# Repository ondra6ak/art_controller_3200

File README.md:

Art Controller 3200
===================

Simple board with ATmega32u4 and isolated DMX512 interface

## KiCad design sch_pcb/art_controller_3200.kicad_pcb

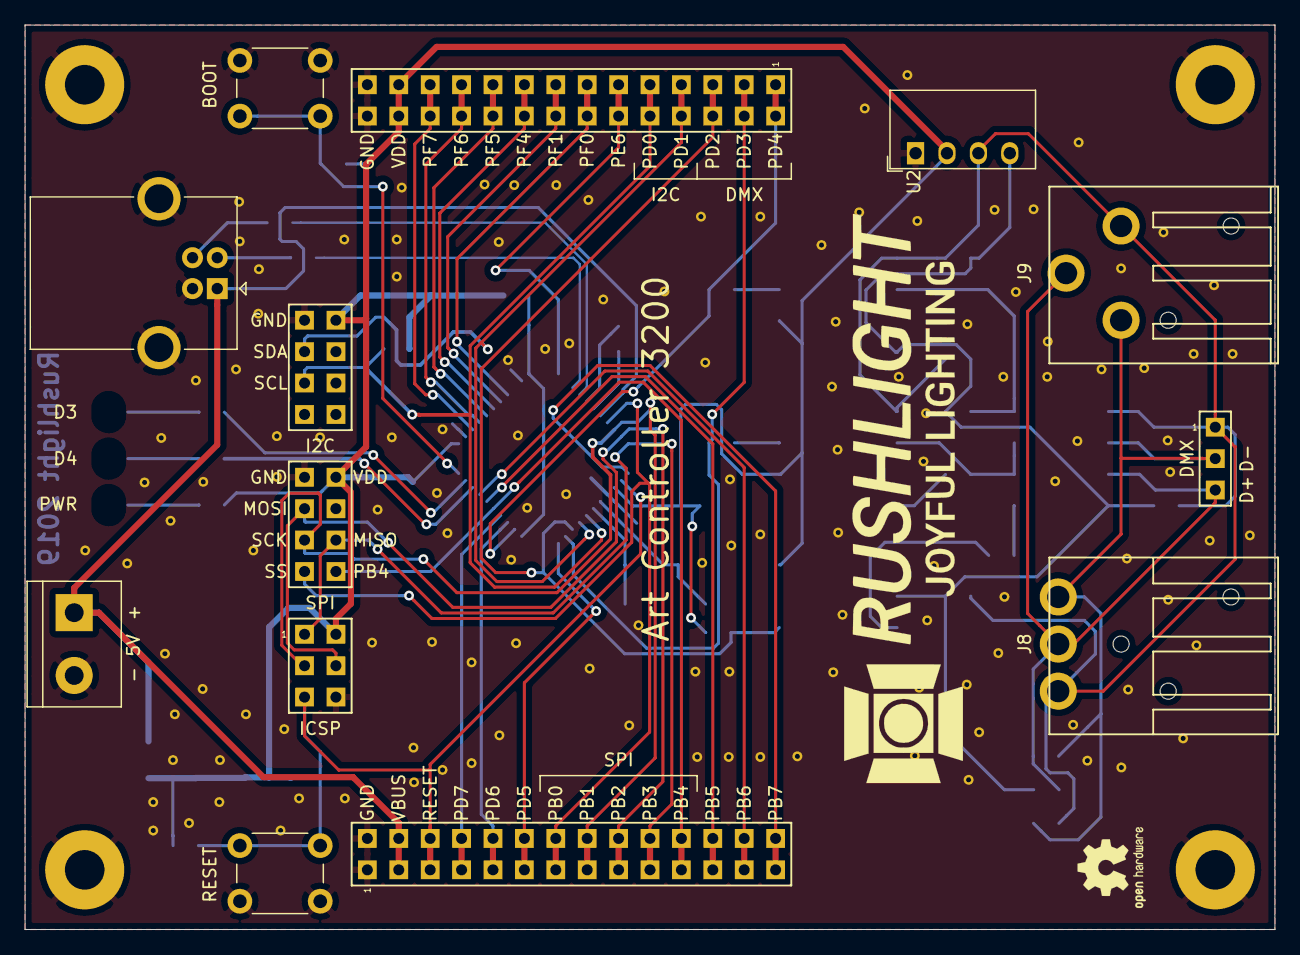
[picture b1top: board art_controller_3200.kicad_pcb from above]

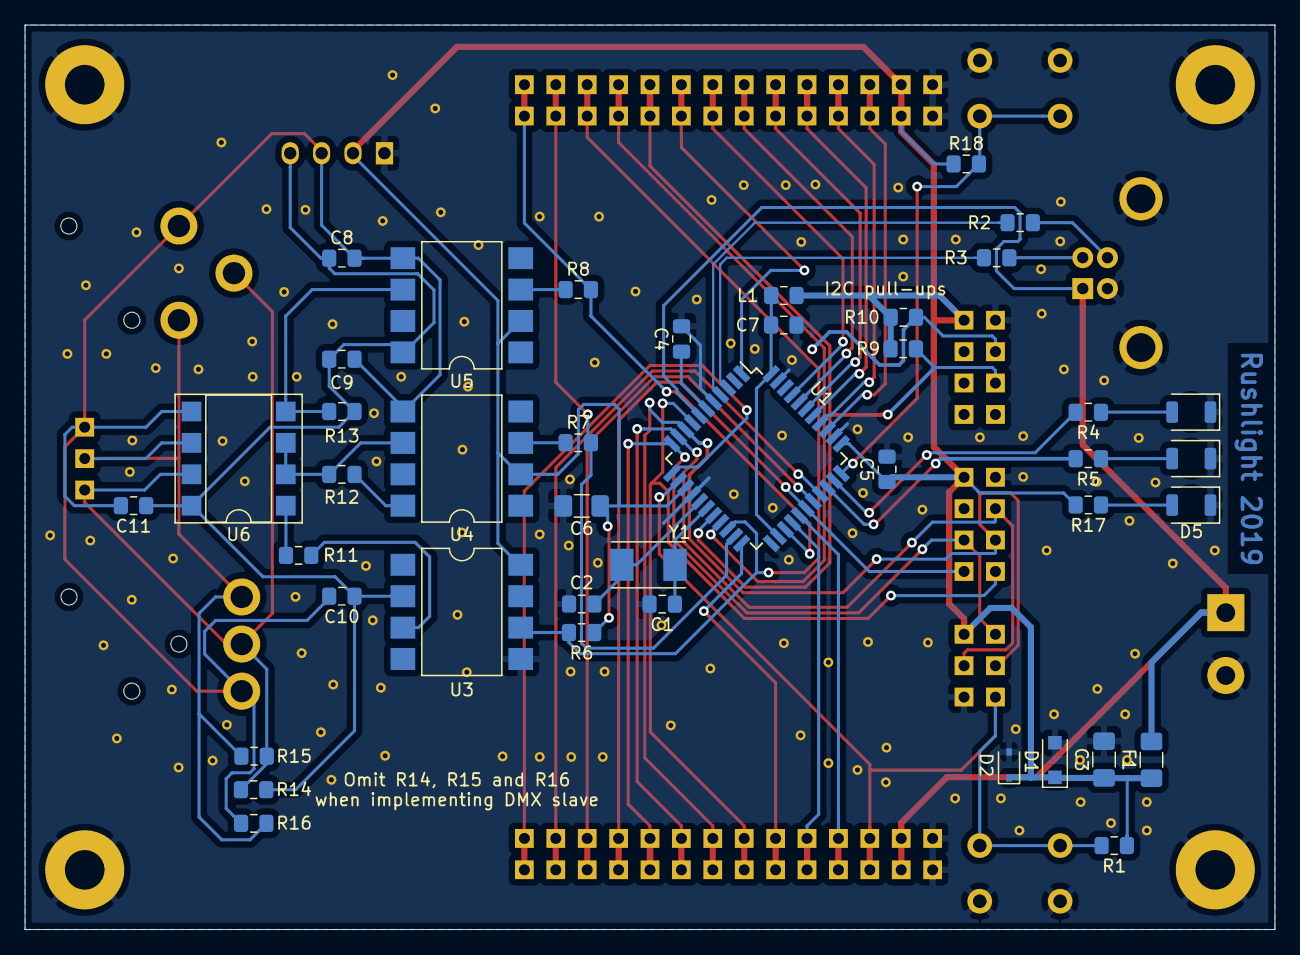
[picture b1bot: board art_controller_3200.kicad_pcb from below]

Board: 2 copper layers, 101.1 x 73.2 mm, 59 parts (42 on the bottom side), 52 nets.

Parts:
C1, C2: 22p; C_0805_2012Metric_Pad1.15x1.40mm_HandSolder
C3: 10u/6V3; C_1206_3216Metric_Pad1.42x1.75mm_HandSolder
C4: 1u; C_0805_2012Metric_Pad1.15x1.40mm_HandSolder
C5, C7, C8, C9, C10, C11: 100n; C_0805_2012Metric_Pad1.15x1.40mm_HandSolder
C6: 4.7u; C_1206_3216Metric_Pad1.42x1.75mm_HandSolder
D1: S1MFL; D_SOD-123F
D2: 5.6V; D_SOD-323
D3: RED; LED_1206_3216Metric_ReverseMount_Hole1.8x2.4mm
D4, D5: GREEN; LED_1206_3216Metric_ReverseMount_Hole1.8x2.4mm
F1: 500m; Fuse_1206_3216Metric_Pad1.42x1.75mm_HandSolder
H1, H2, H3, H4: MountingHole_Pad; MountingHole_3.2mm_M3_Pad
J1: 5V; TerminalBlock_bornier-2_P5.08mm
J2: USB_B; USB_B_OST_USB-B1HSxx_Horizontal
J3, J5: HEADER_2x14_PARALLEL; Straight_2x14
J4: I2C; Straight_2x04
J6: SPI; Straight_2x04
J7: ICSP; Straight_2x03
J8: DMX_IN; NC3MAAH
J9: DMX_OUT; NC3FAAH
J10: DMX; Straight_1x03
L1: 10u; L_0805_2012Metric_Pad1.15x1.40mm_HandSolder
R1, R9, R10, R18: 10k; R_0805_2012Metric_Pad1.15x1.40mm_HandSolder
R2, R3: 22; R_0805_2012Metric_Pad1.15x1.40mm_HandSolder
R4: 2k2; R_0805_2012Metric_Pad1.15x1.40mm_HandSolder
R5, R17: 150; R_0805_2012Metric_Pad1.15x1.40mm_HandSolder
R6, R12, R13: 4k7; R_0805_2012Metric_Pad1.15x1.40mm_HandSolder
R7, R8, R11: 470; R_0805_2012Metric_Pad1.15x1.40mm_HandSolder
R14, R16: 562; R_0805_2012Metric_Pad1.15x1.40mm_HandSolder
R15: 133; R_0805_2012Metric_Pad1.15x1.40mm_HandSolder
SW1: RESET; SW_PUSH_6mm
SW2: BOOT; SW_PUSH_6mm
U1: ATmega32U4-AU; TQFP-44_10x10mm_P0.8mm
U2: CRE1S0505SC; Converter_DCDC_muRata_CRE1xxxxxx3C_THT
U3, U4, U5: 6N137SM; SMDIP-8_W9.53mm
U6: MAX481; DIP-8_W7.62mm_SMDSocket_SmallPads
Y1: 8MHz; Crystal_SMD_Abracon_ABM7-2Pin_6.0x3.5mm

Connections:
/D+: R2.1, U1.4
/D-: R3.2, U1.3
/GND2: C8.2, C9.2, C10.2, C11.2, J8.1, J9.1, J10.1, R16.2, U2.3, U4.5, U5.5, U6.5
/MISO: J3.19, J3.20, J6.6, J7.1, U1.11
/MOSI: J3.17, J3.18, J6.3, J7.4, U1.10
/PB0: J3.13, J3.14, J6.7, U1.8
/PB1: J3.15, J3.16, J6.5, J7.3, U1.9
/PB4: J3.21, J3.22, J6.8, U1.28
/PB5: J3.23, J3.24, U1.29
/PB6: J3.25, J3.26, U1.30
/PB7: J3.27, J3.28, U1.12
/PD0: J4.5, J5.9, J5.10, R9.2, U1.18
/PD1: J4.3, J5.7, J5.8, R10.2, U1.19
/PD2: J5.5, J5.6, R6.2, U1.20, U3.6
/PD3: J5.3, J5.4, R7.2, U1.21
/PD4: J5.1, J5.2, R8.2, U1.25
/PD5: J3.11, J3.12, U1.22
/PD6: J3.9, J3.10, U1.26
/PD7: J3.7, J3.8, U1.27
/PE6: J5.11, J5.12, U1.1
/PF0: J5.13, J5.14, U1.41
/PF1: J5.15, J5.16, U1.40
/PF4: J5.17, J5.18, U1.39
/PF5: J5.19, J5.20, U1.38
/PF6: J5.21, J5.22, U1.37
/PF7: J5.23, J5.24, U1.36
/RESET: J3.5, J3.6, J7.5, R1.2, SW1.2, U1.13
/VDD2: C8.1, C9.1, C10.1, C11.1, R13.2, R14.1, U2.4, U3.2, U5.8, U6.8
GND: C1.2, C2.2, C3.2, C4.2, C5.2, C6.2, C7.2, D1.2, D2.2, D3.1, D4.1, D5.1, H1.1, H2.1, H3.1, H4.1, J1.2, J2.4, J2.5, J3.1, J3.2, J4.1, J5.27, J5.28, J6.1, J7.6, SW1.1, SW2.2, U1.5, U1.15, U1.23, U1.35, U1.43, U2.1, U3.5
unnamed: C1.1, U1.17, Y1.1
unnamed: C2.1, U1.16, Y1.2
unnamed: C4.1, U1.6
unnamed: D3.2, R4.1
unnamed: D4.2, R5.1
unnamed: D5.2, R17.1
unnamed: J2.2, R3.1
unnamed: J2.3, R2.2
unnamed: J8.2, J9.2, J10.2, R15.2, R16.1, U6.6
unnamed: J8.3, J9.3, J10.3, R14.2, R15.1, U6.7
unnamed: R4.2, U1.32
unnamed: R5.2, U1.31
unnamed: R7.1, U4.3
unnamed: R8.1, U5.3
unnamed: R11.1, U6.1
unnamed: R11.2, U3.3
unnamed: R12.1, U4.6, U6.2, U6.3
unnamed: R12.2, U4.8
unnamed: R13.1, U5.6, U6.4
unnamed: R18.2, SW2.1, U1.33
VBUS: F1.2, J1.1, J2.1, J3.3, J3.4, U1.7
VDD: C3.1, C5.1, C6.1, D1.1, D2.1, F1.1, J4.2, J5.25, J5.26, J6.2, J7.2, L1.1, R1.1, R6.1, R9.1, R10.1, R17.2, R18.1, U1.14, U1.34, U2.2, U3.8, U4.2, U5.2
VDDA: C7.1, L1.2, U1.24, U1.44

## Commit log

2019-07-22 Updated render
2019-08-09 Schematic ploted in b/w
